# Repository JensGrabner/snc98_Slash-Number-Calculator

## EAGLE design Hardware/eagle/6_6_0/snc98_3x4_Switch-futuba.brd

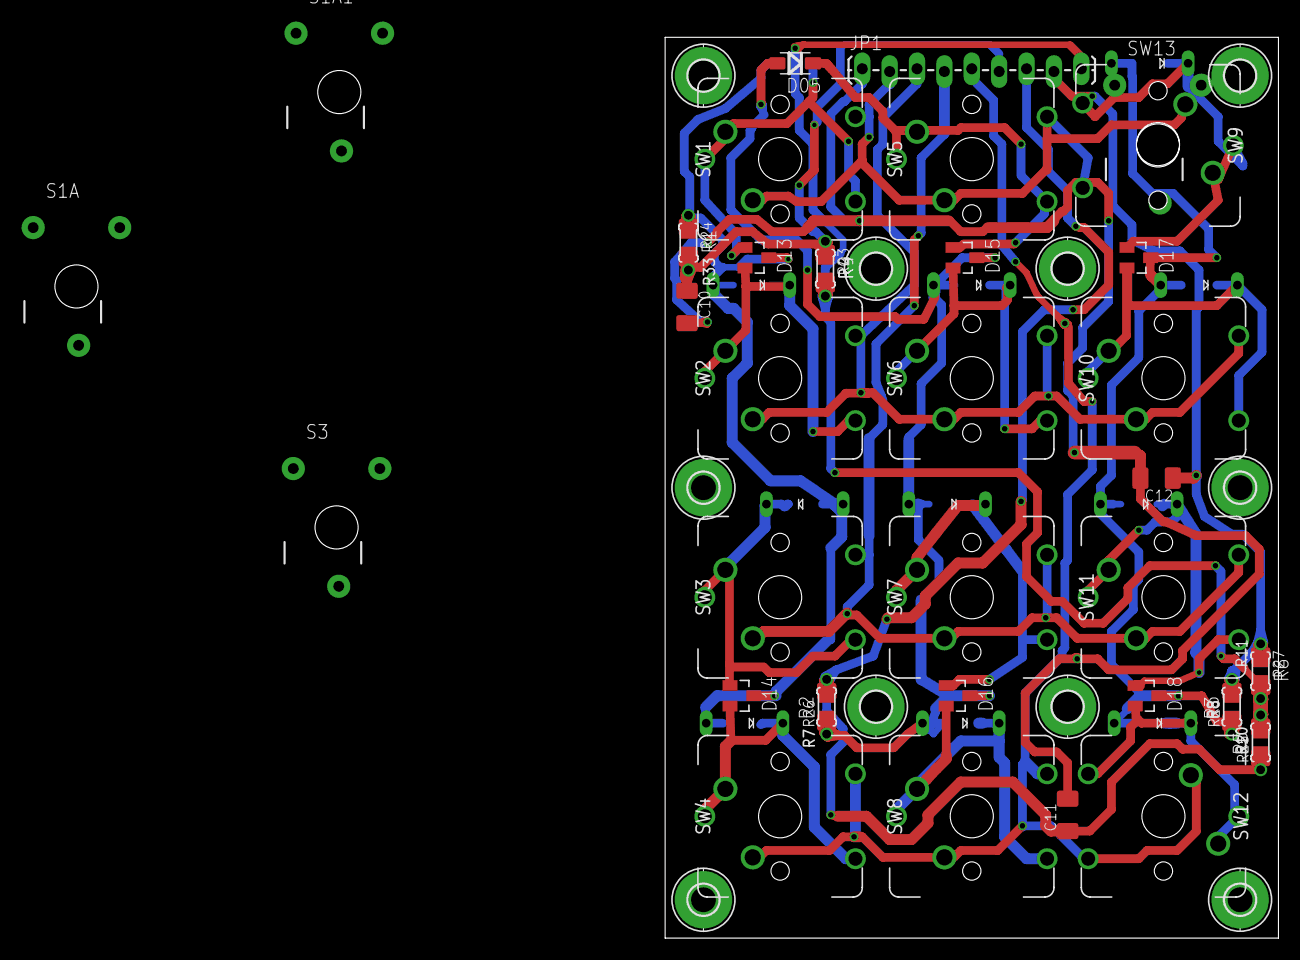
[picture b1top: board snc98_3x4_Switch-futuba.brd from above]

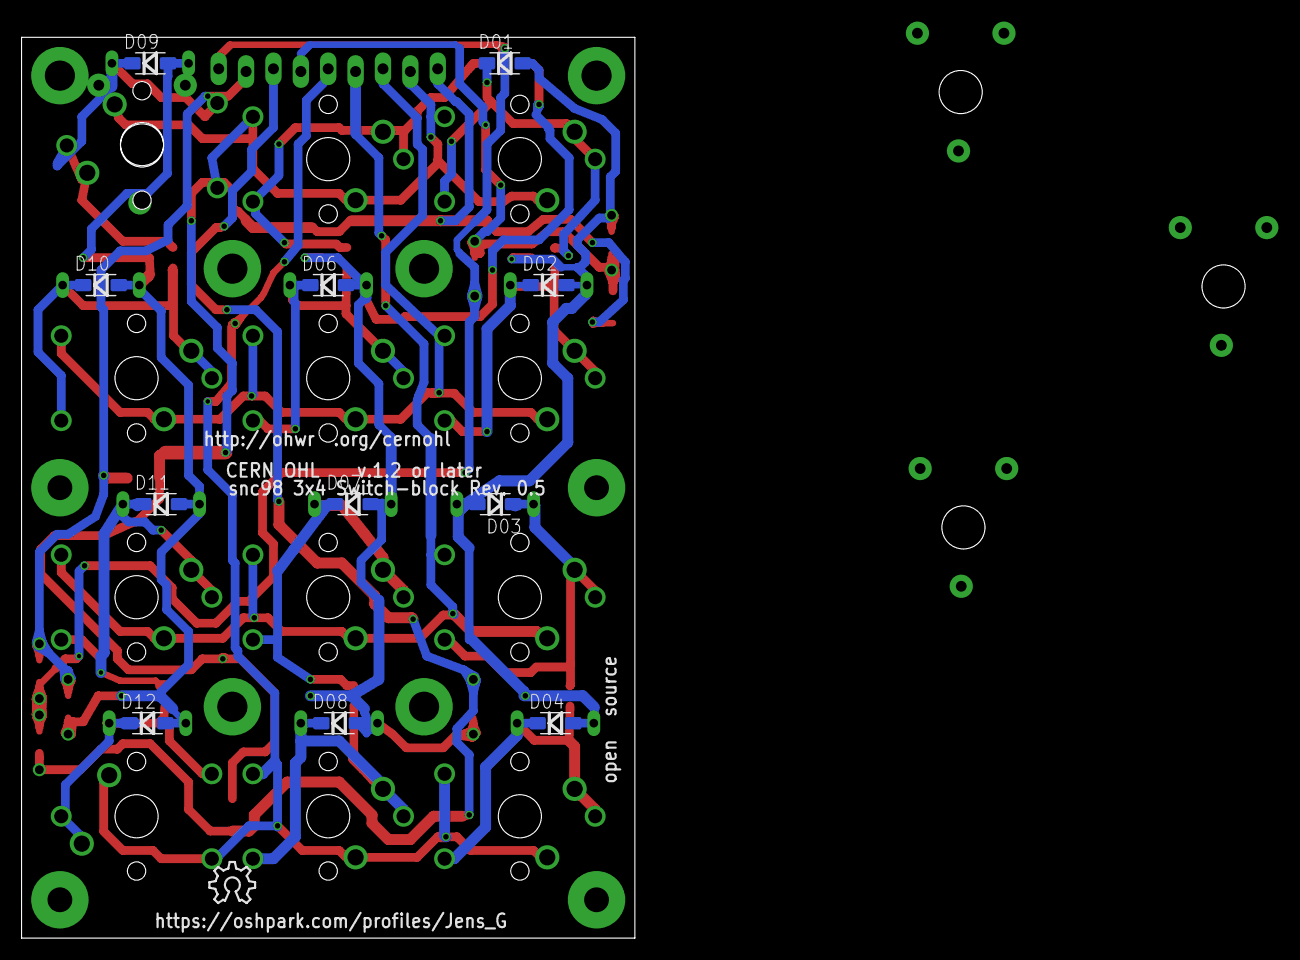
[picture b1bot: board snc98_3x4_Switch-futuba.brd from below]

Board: 2 copper layers, 56.9 x 83.6 mm, 77 parts (12 on the bottom side), 24 nets.

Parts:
C10, C11, C12: 15n; C1206K
D01, D02, D03, D04, D05, D06, D07, D08, D09: SD103AW-DIO; SOD-123F
D10, D11, D12: SD103CW; SOD-123F
D13, D14, D15, D16, D17, D18: BAT54A; SOT23
D19, D20, D21, D22, D23, D24, D25, D26, D27, D28: SD103C; 280MIL-TH
H1, H4, H5, H6, H7, H8: MOUNT-PAD-ROUND2.8; 2,8-PAD
H2, H3, H9, H10: MOUNT-PAD-ROUND2.3; 2,3-PAD
JP1: M09LOCK-LONGPADS; 1X09_LOCK_LONGPADS
LOGO1: OSHW_LOGO_8MILX0150-NT; OSHW_8X150_NOTEXT
R1, R2, R3: 6k8; R1206
R4, R5, R6: 27k; R1206
R7, R8, R33: 6k8; M0805
R9, R10, R11: 27k; M0805
R23, R25, R27: 27k; 0204/5
R24, R26, R28: 6k8; 0204/5
S1A, S1A1, S3: MX1A-XXNN
SW1, SW2, SW3, SW4, SW5, SW6, SW7, SW8, SW9, SW10, SW11, SW12: CHERRY_MX_WITH_FIXING_PINS; MX1A-XXNW
SW13: CHERRY_MX; MX1A-XXNN

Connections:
A1: C10.1, JP1.6, R1.2, R4.1, R9.1, R23.1, R24.2, R33.2
A2: C11.1, JP1.7, R2.2, R5.1, R7.2, R10.1, R25.1, R26.2
A3: C12.1, JP1.8, R3.2, R6.1, R8.2, R11.1, R27.1, R28.2
AREF: JP1.9, R4.2, R5.2, R6.2, R9.2, R10.2, R11.2, R23.2, R25.2, R27.2
A_1: D01.A, D02.A, D03.A, D04.A, D13.3, D14.3, D19.P$1, D20.P$1, D21.P$1, R1.1, R24.1, R33.1
A_2: D05.A, D06.A, D07.A, D08.A, D15.3, D16.3, D22.P$1, D23.P$1, D24.P$1, R2.1, R7.1, R26.1
A_3: D09.A, D10.A, D11.A, D12.A, D17.3, D18.3, D25.P$1, D26.P$1, D27.P$1, D28.P$1, R3.1, R8.1, R28.1
C1: JP1.2, SW1.1, SW1.3, SW5.1, SW5.3, SW9.1, SW9.3
C2: JP1.3, SW2.1, SW2.3, SW6.1, SW6.3, SW10.1, SW10.3
C3: JP1.4, SW3.1, SW3.3, SW7.1, SW7.3, SW11.1, SW11.3
C4: JP1.5, SW4.1, SW4.3, SW8.1, SW8.3, SW12.1, SW12.3
GND: C10.2, C11.2, C12.2, JP1.1
unnamed: D04.C, D14.2, D21.P$2, SW4.2, SW4.4, SW4.5
unnamed: D01.C, D13.1, SW1.2, SW1.4, SW1.5
unnamed: D09.C, D17.1, D25.P$2, SW9.2, SW9.4, SW9.5
unnamed: D10.C, D17.2, D26.P$2, SW10.2, SW10.4, SW10.5
unnamed: D02.C, D13.2, D19.P$2, SW2.2, SW2.4, SW2.5
unnamed: D11.C, D18.1, D27.P$2, SW11.2, SW11.4, SW11.5
unnamed: D12.C, D18.2, D28.P$2, SW12.2, SW12.4, SW12.5
unnamed: D05.C, D15.1, SW5.2, SW5.4, SW5.5
unnamed: D06.C, D15.2, D22.P$2, SW6.2, SW6.4, SW6.5
unnamed: D07.C, D16.1, D23.P$2, SW7.2, SW7.4, SW7.5
unnamed: D08.C, D16.2, D24.P$2, SW8.2, SW8.4, SW8.5
unnamed: D03.C, D14.1, D20.P$2, SW3.2, SW3.4, SW3.5

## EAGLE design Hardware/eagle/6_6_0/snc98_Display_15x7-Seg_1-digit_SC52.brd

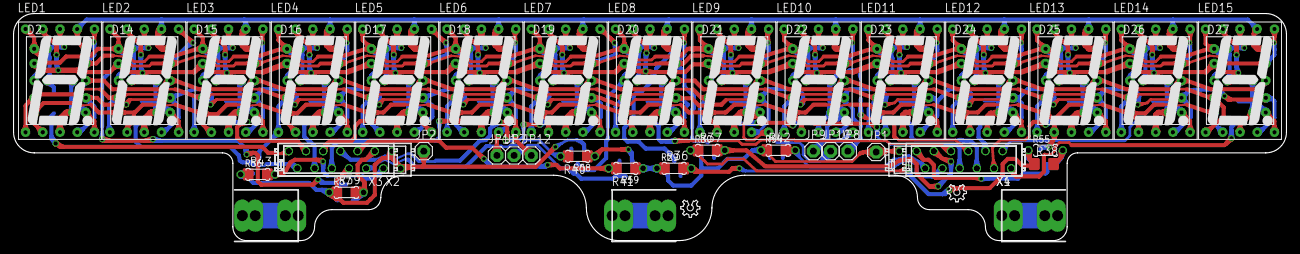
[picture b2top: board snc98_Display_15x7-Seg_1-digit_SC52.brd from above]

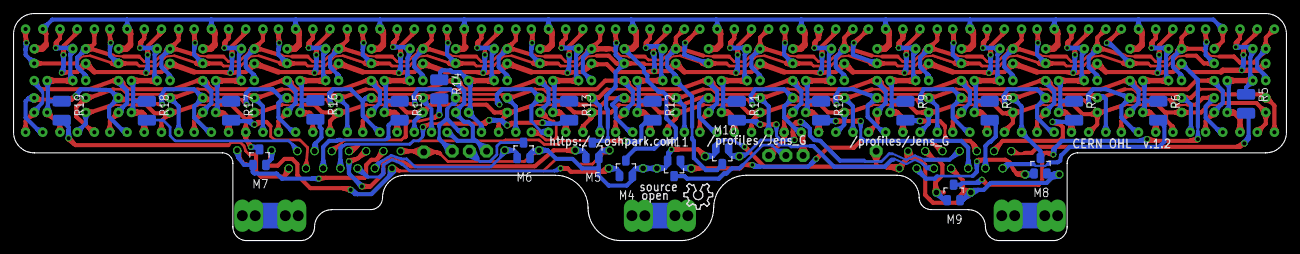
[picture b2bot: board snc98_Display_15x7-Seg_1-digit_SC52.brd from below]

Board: 2 copper layers, 188.0 x 33.5 mm, 87 parts (24 on the bottom side), 52 nets.

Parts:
BH4, BH5: HOLDER_AAA_LEFT1; BATTERY-AAA-LEFT
BH6: HOLDER_AAA_RIGHT; BATTERY-AAA-RIGHT
D2, D14, D15, D16, D17, D18, D19, D20, D21, D22, D23, D24, D25, D26, D27: SC40-11_UNISC40-11_UNI; 10MM_UNI
JP1, JP2, JP7, JP8, JP9, JP10, JP11, JP12: 1X01
LED1, LED2, LED3, LED4, LED5, LED6, LED7, LED8, LED9, LED10, LED11, LED12, LED13, LED14, LED15: 7-SEG_SC52-11; SA52-11
LOGO1: OSHW_LOGO_8MILX0150-NT; OSHW_8X150_NOTEXT
LOGO2, LOGO3: OSHW_LOGO_6MILX0100-NT; OSHW_6X100_NOTEXT
M4, M5, M6, M7, M8, M9, M10, M11: IRLML2244; SOT-23
R5, R6, R7, R8, R9, R10, R11, R12, R13, R14, R15, R16, R17, R18, R19: 22; R1210
R29, R30, R54, R55, R56, R57, R58, R59: 3k3; 0204/5
R36, R37, R38, R39, R40, R41, R42, R43: 3k3; R1206
X1, X3: MICROMATCH-12
X2, X4: MICROMATCH-14

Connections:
CA_LED: JP1.1, JP2.1, M4.2, M5.2, M6.2, M7.2, M8.2, M9.2, M10.2, M11.2, R29.1, R30.1, R36.1, R37.1, R38.1, R39.1, R40.1, R41.1, R42.1, R43.1, R54.1, R55.1, R56.1, R57.1, R58.1, R59.1, X2.8, X2.13, X2.14, X3.8, X4.1, X4.2
D0_A: R5.2, X2.1, X3.1
D1_A: R6.2, X2.2, X3.2
D2_A: R7.2, X2.3, X3.3
D3_A: R8.2, X2.4, X3.4
D4_A: R9.2, X2.5, X3.5
D5_A: R10.2, X2.6, X3.6
D6_A: R11.2, X2.7, X3.7
D7_A: R12.2, X1.5, X4.7
D8_A: R13.2, X1.6, X4.8
D9_A: R14.2, X1.7, X4.9
D10_A: R15.2, X1.8, X4.10
D11_A: R16.2, X1.9, X4.11
D12_A: R17.2, X1.10, X4.12
D13_A: R18.2, X1.11, X4.13
D14_A: R19.2, X1.12, X4.14
DIG_0: D2.11, D2.12, D2.13, D2.14, LED1.3, LED1.8, R5.1
DIG_1: D14.11, D14.12, D14.13, D14.14, LED2.3, LED2.8, R6.1
DIG_2: D15.11, D15.12, D15.13, D15.14, LED3.3, LED3.8, R7.1
DIG_3: D16.11, D16.12, D16.13, D16.14, LED4.3, LED4.8, R8.1
DIG_4: D17.11, D17.12, D17.13, D17.14, LED5.3, LED5.8, R9.1
DIG_5: D18.11, D18.12, D18.13, D18.14, LED6.3, LED6.8, R10.1
DIG_6: D19.11, D19.12, D19.13, D19.14, LED7.3, LED7.8, R11.1
DIG_7: D20.11, D20.12, D20.13, D20.14, LED8.3, LED8.8, R12.1
DIG_8: D21.11, D21.12, D21.13, D21.14, LED9.3, LED9.8, R13.1
DIG_9: D22.11, D22.12, D22.13, D22.14, LED10.3, LED10.8, R14.1
DIG_10: D23.11, D23.12, D23.13, D23.14, LED11.3, LED11.8, R15.1
DIG_11: D24.11, D24.12, D24.13, D24.14, LED12.3, LED12.8, R16.1
DIG_12: D25.11, D25.12, D25.13, D25.14, LED13.3, LED13.8, R17.1
DIG_13: D26.11, D26.12, D26.13, D26.14, LED14.3, LED14.8, R18.1
DIG_14: D27.11, D27.12, D27.13, D27.14, LED15.3, LED15.8, R19.1
IO-A: M4.1, R29.2, R36.2, X1.4, X4.6
IO-B: M5.1, R30.2, R37.2, X1.3, X4.5
IO-C: M6.1, R42.2, R54.2, X1.2, X4.4
IO-D: M7.1, R38.2, R55.2, X1.1, X4.3
IO-DP: M11.1, R41.2, R59.2, X2.9, X3.9
IO-E: M8.1, R43.2, R56.2, X2.12, X3.12
IO-F: M9.1, R39.2, R57.2, X2.11, X3.11
IO-G: M10.1, R40.2, R58.2, X2.10, X3.10
NC1: BH4.P1, BH4.P2, BH4.P3, BH4.P4
NC2: BH5.P1, BH5.P2, BH5.P3, BH5.P4
NC3: BH6.M1, BH6.M2, BH6.M3, BH6.M4
SEG_A: D2.10, D14.10, D15.10, D16.10, D17.10, D18.10, D19.10, D20.10, D21.10, D22.10, D23.10, D24.10, D25.10, D26.10, D27.10, LED1.7, LED2.7, LED3.7, LED4.7, LED5.7, LED6.7, LED7.7, LED8.7, LED9.7, LED10.7, LED11.7, LED12.7, LED13.7, LED14.7, LED15.7, M4.3
SEG_B: D2.9, D14.9, D15.9, D16.9, D17.9, D18.9, D19.9, D20.9, D21.9, D22.9, D23.9, D24.9, D25.9, D26.9, D27.9, LED1.6, LED2.6, LED3.6, LED4.6, LED5.6, LED6.6, LED7.6, LED8.6, LED9.6, LED10.6, LED11.6, LED12.6, LED13.6, LED14.6, LED15.6, M5.3
SEG_C: D2.7, D14.7, D15.7, D16.7, D17.7, D18.7, D19.7, D20.7, D21.7, D22.7, D23.7, D24.7, D25.7, D26.7, D27.7, JP8.1, JP11.1, LED1.4, LED2.4, LED3.4, LED4.4, LED5.4, LED6.4, LED7.4, LED8.4, LED9.4, LED10.4, LED11.4, LED12.4, LED13.4, LED14.4, LED15.4
SEG_C_SOURCE: JP10.1, M6.3
SEG_D: D2.5, D14.5, D15.5, D16.5, D17.5, D18.5, D19.5, D20.5, D21.5, D22.5, D23.5, D24.5, D25.5, D26.5, D27.5, LED1.2, LED2.2, LED3.2, LED4.2, LED5.2, LED6.2, LED7.2, LED8.2, LED9.2, LED10.2, LED11.2, LED12.2, LED13.2, LED14.2, LED15.2, M7.3
SEG_DP: D2.6, D2.8, D14.6, D14.8, D15.6, D15.8, D16.6, D16.8, D17.6, D17.8, D18.6, D18.8, D19.6, D19.8, D20.6, D20.8, D21.6, D21.8, D22.6, D22.8, D23.6, D23.8, D24.6, D24.8, D25.6, D25.8, D26.6, D26.8, D27.6, D27.8, JP9.1, JP12.1, LED1.5, LED2.5, LED3.5, LED4.5, LED5.5, LED6.5, LED7.5, LED8.5, LED9.5, LED10.5, LED11.5, LED12.5, LED13.5, LED14.5, LED15.5
SEG_DP_SOURCE: JP7.1, M11.3
SEG_E: D2.4, D14.4, D15.4, D16.4, D17.4, D18.4, D19.4, D20.4, D21.4, D22.4, D23.4, D24.4, D25.4, D26.4, D27.4, LED1.1, LED2.1, LED3.1, LED4.1, LED5.1, LED6.1, LED7.1, LED8.1, LED9.1, LED10.1, LED11.1, LED12.1, LED13.1, LED14.1, LED15.1, M8.3
SEG_F: D2.2, D14.2, D15.2, D16.2, D17.2, D18.2, D19.2, D20.2, D21.2, D22.2, D23.2, D24.2, D25.2, D26.2, D27.2, LED1.9, LED2.9, LED3.9, LED4.9, LED5.9, LED6.9, LED7.9, LED8.9, LED9.9, LED10.9, LED11.9, LED12.9, LED13.9, LED14.9, LED15.9, M9.3
SEG_G: D2.1, D2.3, D14.1, D14.3, D15.1, D15.3, D16.1, D16.3, D17.1, D17.3, D18.1, D18.3, D19.1, D19.3, D20.1, D20.3, D21.1, D21.3, D22.1, D22.3, D23.1, D23.3, D24.1, D24.3, D25.1, D25.3, D26.1, D26.3, D27.1, D27.3, LED1.10, LED2.10, LED3.10, LED4.10, LED5.10, LED6.10, LED7.10, LED8.10, LED9.10, LED10.10, LED11.10, LED12.10, LED13.10, LED14.10, LED15.10, M10.3

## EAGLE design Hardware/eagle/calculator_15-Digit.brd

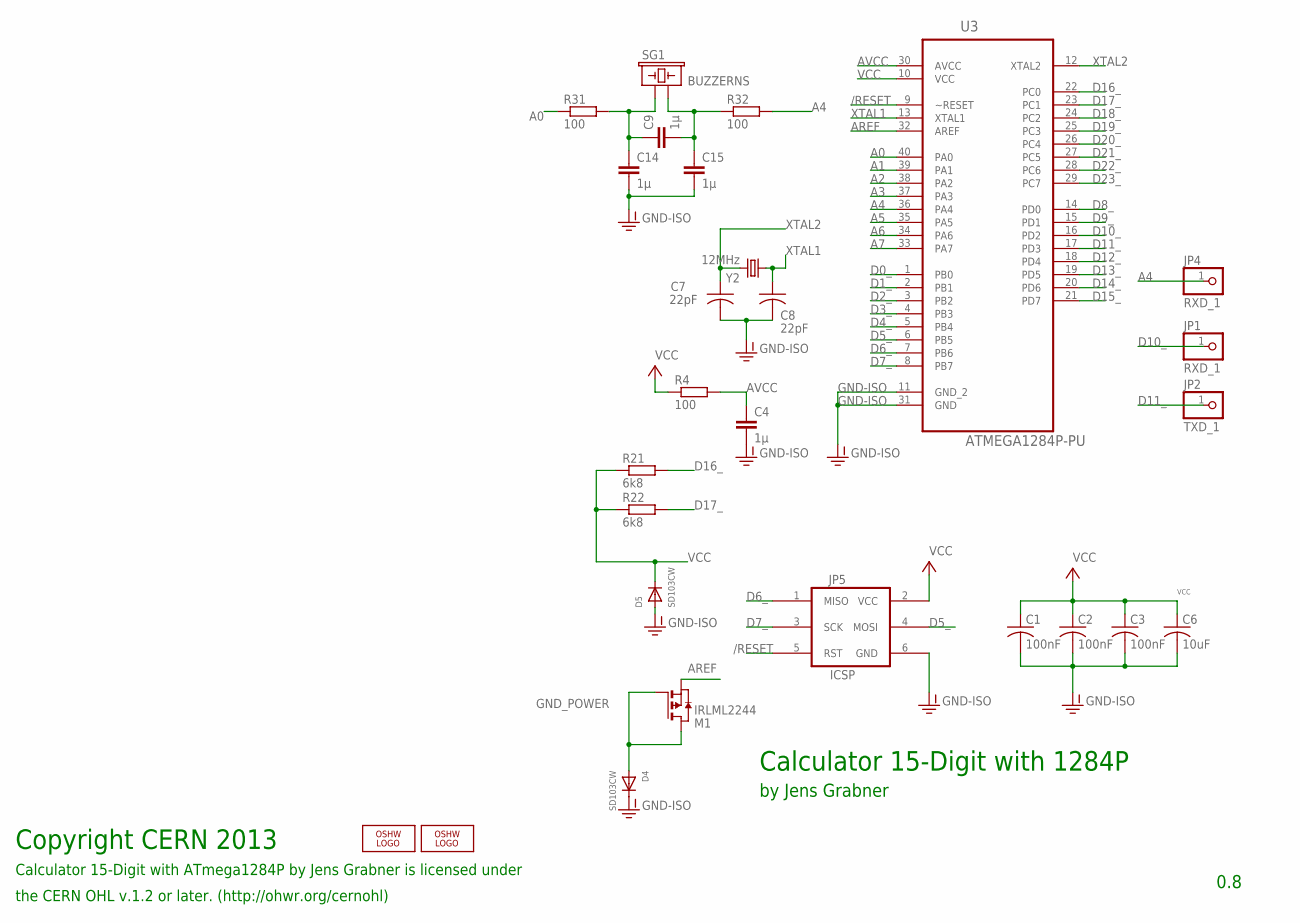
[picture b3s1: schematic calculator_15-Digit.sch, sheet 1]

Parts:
C1, C2, C3: 100nF; C025_050-025X075
C4, C9, C14, C15: 1µ; C025_050-025X075
C6: 10uF; C025_050-025X075
C7, C8: 22pF; C025-024X044
D4, D5: SD103CW; SMADIODE
JP1, JP4: RXD_1; 1X01-CLEANBIG
JP2: TXD_1; 1X01-CLEANBIG
JP5: ICSP; 2X3_LOCK
LOGO1: OSHW_LOGO_8MILX0150-NT; OSHW_8X150_NOTEXT
LOGO2: OSHW_LOGO_6MILX0100-NT; OSHW_6X100_NOTEXT
M1: IRLML2244; SOT-23
R4, R31, R32: 100; 0204/7
R21, R22: 6k8; 0204/7
SG1: BUZZERNS; BUZZER-12MM-NS
U3: ATMEGA1284P-PU; DIP254P1524X483-40
Y2: 12MHz; HC49U-V

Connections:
/RESET: JP5.5 (RST), U3.9 (~RESET); also elsewhere on the board
A0: R31.1, U3.40 (PA0)
A1: U3.39 (PA1); also elsewhere on the board
A2: U3.38 (PA2); also elsewhere on the board
A3: U3.37 (PA3); also elsewhere on the board
A4: JP4.1, R32.2, U3.36 (PA4)
A5: U3.35 (PA5); also elsewhere on the board
A6: U3.34 (PA6); also elsewhere on the board
A7: U3.33 (PA7); also elsewhere on the board
AREF: M1.2 (S), U3.32 (AREF); also elsewhere on the board
AVCC: C4.1, R4.2, U3.30 (AVCC)
D0_: U3.1 (PB0); also elsewhere on the board
D1_: U3.2 (PB1); also elsewhere on the board
D2_: U3.3 (PB2)
D3_: U3.4 (PB3); also elsewhere on the board
D4_: U3.5 (PB4)
D5_: JP5.4 (MOSI), U3.6 (PB5)
D6_: JP5.1 (MISO), U3.7 (PB6); also elsewhere on the board
D7_: JP5.3 (SCK), U3.8 (PB7); also elsewhere on the board
D8_: U3.14 (PD0); also elsewhere on the board
D9_: U3.15 (PD1); also elsewhere on the board
D10_: JP1.1, U3.16 (PD2); also elsewhere on the board
D11_: JP2.1, U3.17 (PD3); also elsewhere on the board
D12_: U3.18 (PD4); also elsewhere on the board
D13_: U3.19 (PD5); also elsewhere on the board
D14_: U3.20 (PD6); also elsewhere on the board
D15_: U3.21 (PD7); also elsewhere on the board
D16_: R21.2, U3.22 (PC0)
D17_: R22.2, U3.23 (PC1)
D18_: U3.24 (PC2); also elsewhere on the board
D19_: U3.25 (PC3); also elsewhere on the board
D20_: U3.26 (PC4); also elsewhere on the board
D21_: U3.27 (PC5); also elsewhere on the board
D22_: U3.28 (PC6); also elsewhere on the board
D23_: U3.29 (PC7); also elsewhere on the board
GND-ISO: C1.2, C2.2, C3.2, C4.2, C6.2, C7.2, C8.2, C14.2, C15.2, D4.C, D5.A, JP5.6 (GND), U3.11 (GND_2), U3.31 (GND); also elsewhere on the board
GND_POWER: D4.A, M1.1 (G), M1.3 (D)
unnamed: C9.2, C15.1, R32.1, SG1.- (2)
unnamed: C9.1, C14.1, R31.2, SG1.+ (1)
VCC: C1.1, C2.1, C3.1, C6.1, D5.C, JP5.2 (VCC), R4.1, R21.1, R22.1, U3.10 (VCC); also elsewhere on the board
XTAL1: C8.1, U3.13 (XTAL1), Y2.1
XTAL2: C7.1, U3.12 (XTAL2), Y2.2

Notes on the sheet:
Calculator 15-Digit with 1284P
by Jens Grabner
0.8
Calculator 15-Digit with ATmega1284P by Jens Grabner is licensed under
Copyright CERN 2013
the CERN OHL v.1.2 or later. (http://ohwr.org/cernohl)

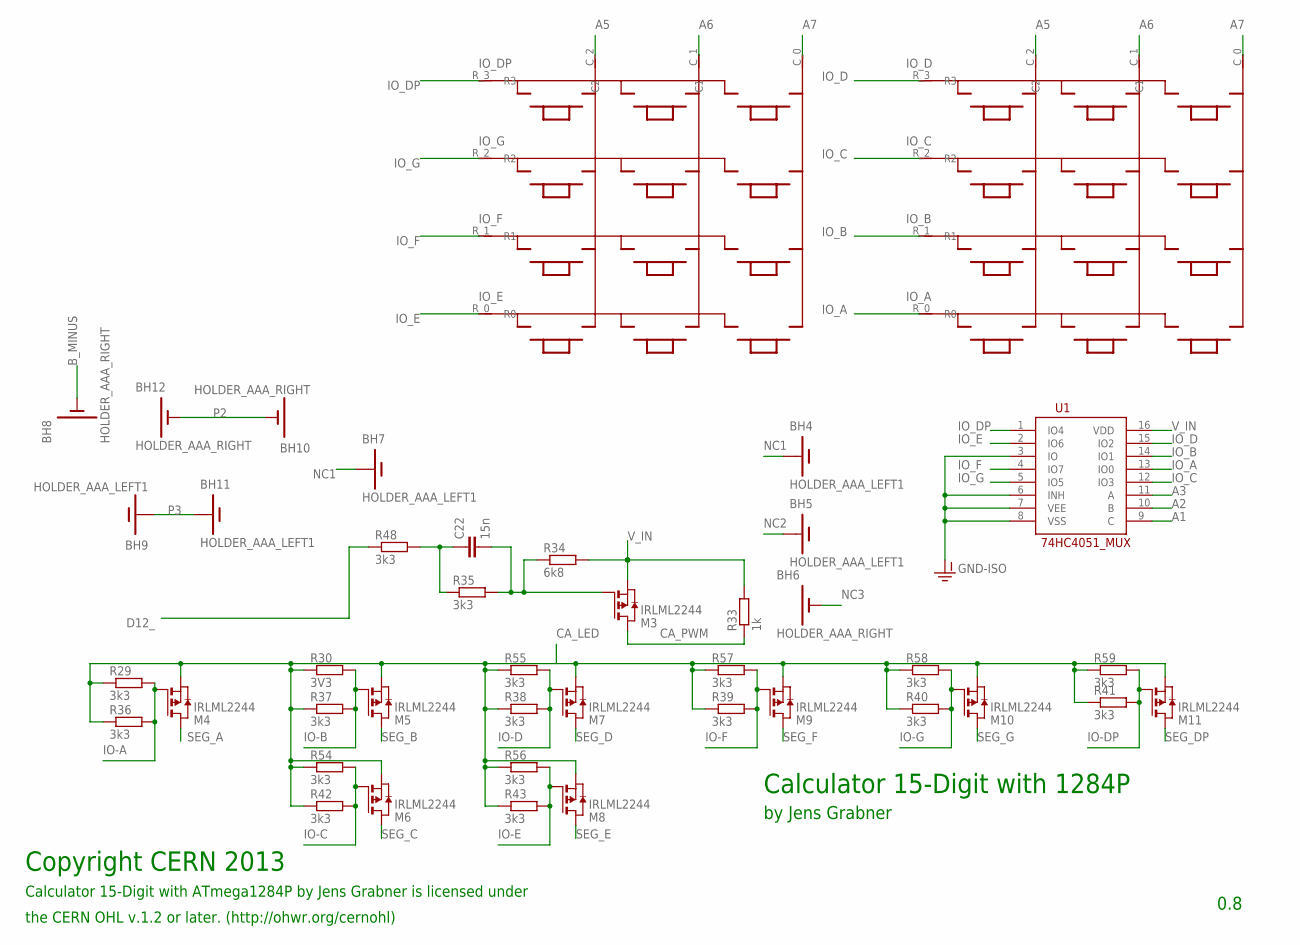
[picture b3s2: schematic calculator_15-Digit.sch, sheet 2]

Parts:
BH4, BH5, BH7, BH9, BH11: HOLDER_AAA_LEFT1; BATTERY-AAA-LEFT
BH6, BH8, BH10, BH12: HOLDER_AAA_RIGHT; BATTERY-AAA-RIGHT
C22: 15n; C1206K
KP1, KP2: KEYPAD
M3, M4, M5, M6, M7, M8, M9, M10, M11: IRLML2244; SOT-23
R29, R54, R55, R56, R57, R58, R59: 3k3; 0204/5
R30: 3V3; 0204/5
R33: 1k; 0204/7
R34: 6k8; 0204/7
R35, R48: 3k3; 0204/7
R36, R37, R38, R39, R40, R41, R42, R43: 3k3; R1206
U1: 74HC4051_MUX; SO16

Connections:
A1: U1.9 (C); also elsewhere on the board
A2: U1.10 (B); also elsewhere on the board
A3: U1.11 (A); also elsewhere on the board
A5: KP1.C_2 (C2), KP2.C_2 (C2); also elsewhere on the board
A6: KP1.C_1 (C1), KP2.C_1 (C1); also elsewhere on the board
A7: KP1.C_0 (C0), KP2.C_0 (C0); also elsewhere on the board
A8: C22.1, R35.1, R48.2
B_MINUS: BH8.M1, BH8.M2, BH8.M3, BH8.M4; also elsewhere on the board
CA_LED: M4.2 (S), M5.2 (S), M6.2 (S), M7.2 (S), M8.2 (S), M9.2 (S), M10.2 (S), M11.2 (S), R29.1, R30.1, R36.1, R37.1, R38.1, R39.1, R40.1, R41.1, R42.1, R43.1, R54.1, R55.1, R56.1, R57.1, R58.1, R59.1; also elsewhere on the board
CA_PWM: M3.3 (D), R33.1; also elsewhere on the board
D12_: R48.1; also elsewhere on the board
GND1: C22.2
GND-ISO: U1.3 (IO), U1.6 (INH), U1.7 (VEE), U1.8 (VSS); also elsewhere on the board
IO-A: M4.1 (G), R29.2, R36.2; also elsewhere on the board
IO-B: M5.1 (G), R30.2, R37.2; also elsewhere on the board
IO-C: M6.1 (G), R42.2, R54.2; also elsewhere on the board
IO-D: M7.1 (G), R38.2, R55.2; also elsewhere on the board
IO-DP: M11.1 (G), R41.2, R59.2; also elsewhere on the board
IO-E: M8.1 (G), R43.2, R56.2; also elsewhere on the board
IO-F: M9.1 (G), R39.2, R57.2; also elsewhere on the board
IO-G: M10.1 (G), R40.2, R58.2; also elsewhere on the board
IO_A: KP2.R_0 (R0), U1.13 (IO0); also elsewhere on the board
IO_B: KP2.R_1 (R1), U1.14 (IO1); also elsewhere on the board
IO_C: KP2.R_2 (R2), U1.12 (IO3); also elsewhere on the board
IO_D: KP2.R_3 (R3), U1.15 (IO2); also elsewhere on the board
IO_DP: KP1.R_3 (R3), U1.1 (IO4); also elsewhere on the board
IO_E: KP1.R_0 (R0), U1.2 (IO6); also elsewhere on the board
IO_F: KP1.R_1 (R1), U1.4 (IO7); also elsewhere on the board
IO_G: KP1.R_2 (R2), U1.5 (IO5); also elsewhere on the board
unnamed: M3.1 (G), R34.1, R35.2
NC1: BH4.P1, BH4.P2, BH4.P3, BH4.P4, BH7.P1, BH7.P2, BH7.P3, BH7.P4
NC2: BH5.P1, BH5.P2, BH5.P3, BH5.P4
NC3: BH6.M1, BH6.M2, BH6.M3, BH6.M4
P2: BH10.M1, BH10.M2, BH10.M3, BH10.M4, BH12.M1, BH12.M2, BH12.M3, BH12.M4
P3: BH9.P1, BH9.P2, BH9.P3, BH9.P4, BH11.P1, BH11.P2, BH11.P3, BH11.P4
SEG_A: M4.3 (D); also elsewhere on the board
SEG_B: M5.3 (D); also elsewhere on the board
SEG_C: M6.3 (D); also elsewhere on the board
SEG_D: M7.3 (D); also elsewhere on the board
SEG_DP: M11.3 (D); also elsewhere on the board
SEG_E: M8.3 (D); also elsewhere on the board
SEG_F: M9.3 (D); also elsewhere on the board
SEG_G: M10.3 (D); also elsewhere on the board
V_IN: M3.2 (S), R33.2, R34.2, U1.16 (VDD); also elsewhere on the board

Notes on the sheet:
Calculator 15-Digit with 1284P
by Jens Grabner
0.8
Calculator 15-Digit with ATmega1284P by Jens Grabner is licensed under
Copyright CERN 2013
the CERN OHL v.1.2 or later. (http://ohwr.org/cernohl)

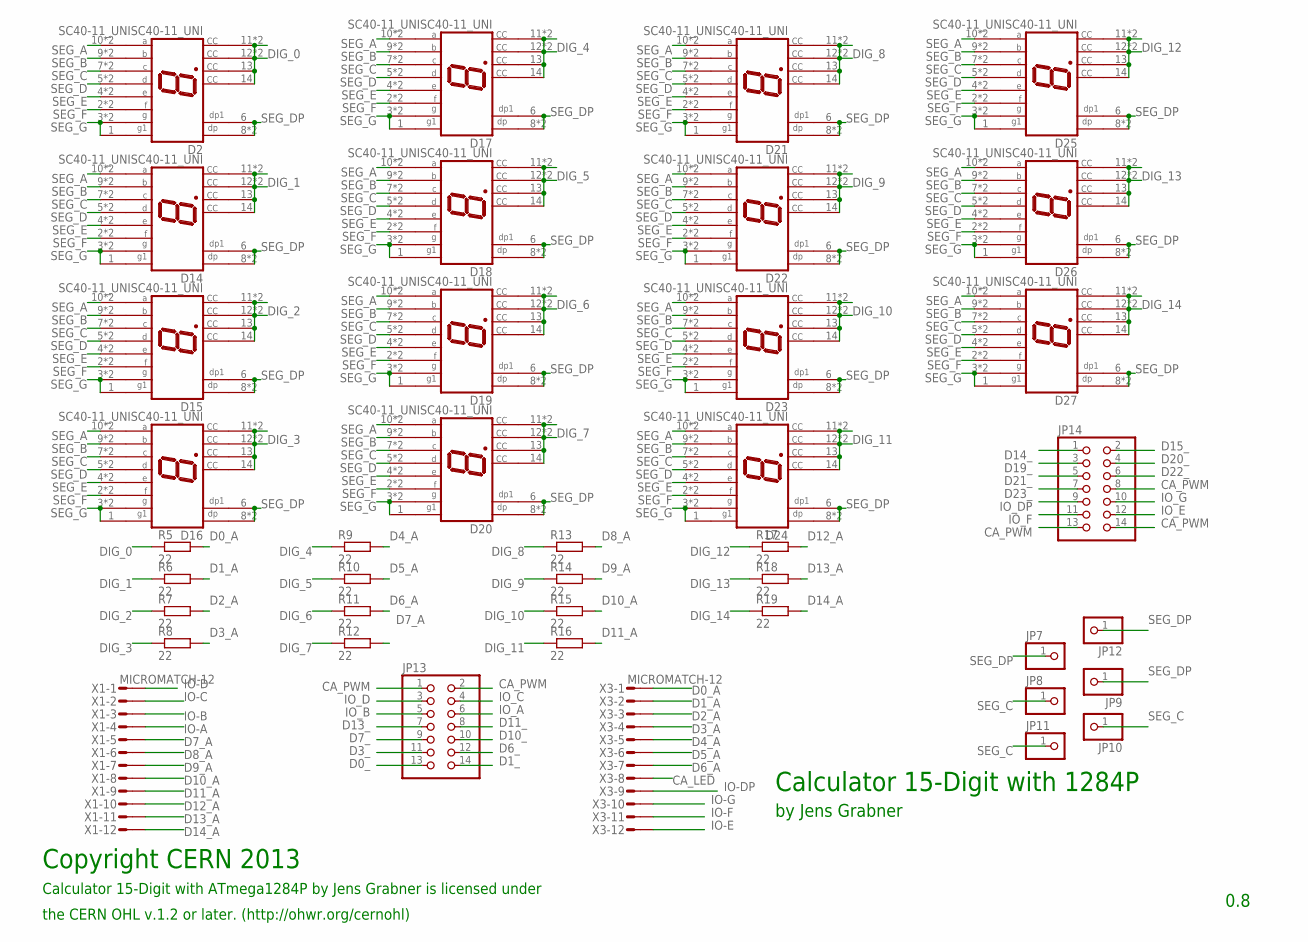
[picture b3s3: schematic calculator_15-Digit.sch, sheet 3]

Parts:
D2, D14, D15, D16, D17, D18, D19, D20, D21, D22, D23, D24, D25, D26, D27: SC40-11_UNISC40-11_UNI; 10MM_UNI
JP7, JP8, JP9, JP10, JP11, JP12: PINHD-1X1; 1X01
JP13, JP14: PINHD-2X7; 2X07
R5, R6, R7, R8, R9, R10, R11, R12, R13, R14, R15, R16, R17, R18, R19: 22; R1210
X1, X3: MICROMATCH-12

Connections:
CA_LED: X3.8; also elsewhere on the board
CA_PWM: JP13.1, JP13.2, JP14.8, JP14.13, JP14.14; also elsewhere on the board
D0_: JP13.13; also elsewhere on the board
D0_A: R5.2, X3.1
D1_: JP13.14; also elsewhere on the board
D1_A: R6.2, X3.2
D2_A: R7.2, X3.3
D3_: JP13.11; also elsewhere on the board
D3_A: R8.2, X3.4
D4_A: R9.2, X3.5
D5_A: R10.2, X3.6
D6_: JP13.12; also elsewhere on the board
D6_A: R11.2, X3.7
D7_: JP13.9; also elsewhere on the board
D7_A: R12.2, X1.5
D8_A: R13.2, X1.6
D9_A: R14.2, X1.7
D10_: JP13.10; also elsewhere on the board
D10_A: R15.2, X1.8
D11_: JP13.8; also elsewhere on the board
D11_A: R16.2, X1.9
D12_A: R17.2, X1.10
D13_: JP13.7; also elsewhere on the board
D13_A: R18.2, X1.11
D14_: JP14.1; also elsewhere on the board
D14_A: R19.2, X1.12
D15_: JP14.2; also elsewhere on the board
D19_: JP14.3; also elsewhere on the board
D20_: JP14.4; also elsewhere on the board
D21_: JP14.5; also elsewhere on the board
D22_: JP14.6; also elsewhere on the board
D23_: JP14.7; also elsewhere on the board
DIG_0: D2.11 (CC1), D2.12 (CC2), D2.13 (CC3), D2.14 (CC4), D2.23 (CC1), D2.28 (CC2), R5.1
DIG_1: D14.11 (CC1), D14.12 (CC2), D14.13 (CC3), D14.14 (CC4), D14.23 (CC1), D14.28 (CC2), R6.1
DIG_2: D15.11 (CC1), D15.12 (CC2), D15.13 (CC3), D15.14 (CC4), D15.23 (CC1), D15.28 (CC2), R7.1
DIG_3: D16.11 (CC1), D16.12 (CC2), D16.13 (CC3), D16.14 (CC4), D16.23 (CC1), D16.28 (CC2), R8.1
DIG_4: D17.11 (CC1), D17.12 (CC2), D17.13 (CC3), D17.14 (CC4), D17.23 (CC1), D17.28 (CC2), R9.1
DIG_5: D18.11 (CC1), D18.12 (CC2), D18.13 (CC3), D18.14 (CC4), D18.23 (CC1), D18.28 (CC2), R10.1
DIG_6: D19.11 (CC1), D19.12 (CC2), D19.13 (CC3), D19.14 (CC4), D19.23 (CC1), D19.28 (CC2), R11.1
DIG_7: D20.11 (CC1), D20.12 (CC2), D20.13 (CC3), D20.14 (CC4), D20.23 (CC1), D20.28 (CC2), R12.1
DIG_8: D21.11 (CC1), D21.12 (CC2), D21.13 (CC3), D21.14 (CC4), D21.23 (CC1), D21.28 (CC2), R13.1
DIG_9: D22.11 (CC1), D22.12 (CC2), D22.13 (CC3), D22.14 (CC4), D22.23 (CC1), D22.28 (CC2), R14.1
DIG_10: D23.11 (CC1), D23.12 (CC2), D23.13 (CC3), D23.14 (CC4), D23.23 (CC1), D23.28 (CC2), R15.1
DIG_11: D24.11 (CC1), D24.12 (CC2), D24.13 (CC3), D24.14 (CC4), D24.23 (CC1), D24.28 (CC2), R16.1
DIG_12: D25.11 (CC1), D25.12 (CC2), D25.13 (CC3), D25.14 (CC4), D25.23 (CC1), D25.28 (CC2), R17.1
DIG_13: D26.11 (CC1), D26.12 (CC2), D26.13 (CC3), D26.14 (CC4), D26.23 (CC1), D26.28 (CC2), R18.1
DIG_14: D27.11 (CC1), D27.12 (CC2), D27.13 (CC3), D27.14 (CC4), D27.23 (CC1), D27.28 (CC2), R19.1
IO-A: X1.4; also elsewhere on the board
IO-B: X1.3; also elsewhere on the board
IO-C: X1.2; also elsewhere on the board
IO-D: X1.1; also elsewhere on the board
IO-DP: X3.9; also elsewhere on the board
IO-E: X3.12; also elsewhere on the board
IO-F: X3.11; also elsewhere on the board
IO-G: X3.10; also elsewhere on the board
IO_A: JP13.6; also elsewhere on the board
IO_B: JP13.5; also elsewhere on the board
IO_C: JP13.4; also elsewhere on the board
IO_D: JP13.3; also elsewhere on the board
IO_DP: JP14.9; also elsewhere on the board
IO_E: JP14.12; also elsewhere on the board
IO_F: JP14.11; also elsewhere on the board
IO_G: JP14.10; also elsewhere on the board
SEG_A: D2.10 (A), D2.27 (A), D14.10 (A), D14.27 (A), D15.10 (A), D15.27 (A), D16.10 (A), D16.27 (A), D17.10 (A), D17.27 (A), D18.10 (A), D18.27 (A), D19.10 (A), D19.27 (A), D20.10 (A), D20.27 (A), D21.10 (A), D21.27 (A), D22.10 (A), D22.27 (A), D23.10 (A), D23.27 (A), D24.10 (A), D24.27 (A), D25.10 (A), D25.27 (A), D26.10 (A), D26.27 (A), D27.10 (A), D27.27 (A); also elsewhere on the board
SEG_B: D2.9 (B), D2.26 (B), D14.9 (B), D14.26 (B), D15.9 (B), D15.26 (B), D16.9 (B), D16.26 (B), D17.9 (B), D17.26 (B), D18.9 (B), D18.26 (B), D19.9 (B), D19.26 (B), D20.9 (B), D20.26 (B), D21.9 (B), D21.26 (B), D22.9 (B), D22.26 (B), D23.9 (B), D23.26 (B), D24.9 (B), D24.26 (B), D25.9 (B), D25.26 (B), D26.9 (B), D26.26 (B), D27.9 (B), D27.26 (B); also elsewhere on the board
SEG_C: D2.7 (C), D2.24 (C), D14.7 (C), D14.24 (C), D15.7 (C), D15.24 (C), D16.7 (C), D16.24 (C), D17.7 (C), D17.24 (C), D18.7 (C), D18.24 (C), D19.7 (C), D19.24 (C), D20.7 (C), D20.24 (C), D21.7 (C), D21.24 (C), D22.7 (C), D22.24 (C), D23.7 (C), D23.24 (C), D24.7 (C), D24.24 (C), D25.7 (C), D25.24 (C), D26.7 (C), D26.24 (C), D27.7 (C), D27.24 (C), JP8.1, JP10.1, JP11.1; also elsewhere on the board
SEG_D: D2.5 (D), D2.22 (D), D14.5 (D), D14.22 (D), D15.5 (D), D15.22 (D), D16.5 (D), D16.22 (D), D17.5 (D), D17.22 (D), D18.5 (D), D18.22 (D), D19.5 (D), D19.22 (D), D20.5 (D), D20.22 (D), D21.5 (D), D21.22 (D), D22.5 (D), D22.22 (D), D23.5 (D), D23.22 (D), D24.5 (D), D24.22 (D), D25.5 (D), D25.22 (D), D26.5 (D), D26.22 (D), D27.5 (D), D27.22 (D); also elsewhere on the board
SEG_DP: D2.6 (DP1), D2.8 (DP), D2.25 (DP), D14.6 (DP1), D14.8 (DP), D14.25 (DP), D15.6 (DP1), D15.8 (DP), D15.25 (DP), D16.6 (DP1), D16.8 (DP), D16.25 (DP), D17.6 (DP1), D17.8 (DP), D17.25 (DP), D18.6 (DP1), D18.8 (DP), D18.25 (DP), D19.6 (DP1), D19.8 (DP), D19.25 (DP), D20.6 (DP1), D20.8 (DP), D20.25 (DP), D21.6 (DP1), D21.8 (DP), D21.25 (DP), D22.6 (DP1), D22.8 (DP), D22.25 (DP), D23.6 (DP1), D23.8 (DP), D23.25 (DP), D24.6 (DP1), D24.8 (DP), D24.25 (DP), D25.6 (DP1), D25.8 (DP), D25.25 (DP), D26.6 (DP1), D26.8 (DP), D26.25 (DP), D27.6 (DP1), D27.8 (DP), D27.25 (DP), JP7.1, JP9.1, JP12.1; also elsewhere on the board
SEG_E: D2.4 (E), D2.21 (E), D14.4 (E), D14.21 (E), D15.4 (E), D15.21 (E), D16.4 (E), D16.21 (E), D17.4 (E), D17.21 (E), D18.4 (E), D18.21 (E), D19.4 (E), D19.21 (E), D20.4 (E), D20.21 (E), D21.4 (E), D21.21 (E), D22.4 (E), D22.21 (E), D23.4 (E), D23.21 (E), D24.4 (E), D24.21 (E), D25.4 (E), D25.21 (E), D26.4 (E), D26.21 (E), D27.4 (E), D27.21 (E); also elsewhere on the board
SEG_F: D2.2 (F), D2.29 (F), D14.2 (F), D14.29 (F), D15.2 (F), D15.29 (F), D16.2 (F), D16.29 (F), D17.2 (F), D17.29 (F), D18.2 (F), D18.29 (F), D19.2 (F), D19.29 (F), D20.2 (F), D20.29 (F), D21.2 (F), D21.29 (F), D22.2 (F), D22.29 (F), D23.2 (F), D23.29 (F), D24.2 (F), D24.29 (F), D25.2 (F), D25.29 (F), D26.2 (F), D26.29 (F), D27.2 (F), D27.29 (F); also elsewhere on the board
SEG_G: D2.1 (G1), D2.3 (G), D2.30 (G), D14.1 (G1), D14.3 (G), D14.30 (G), D15.1 (G1), D15.3 (G), D15.30 (G), D16.1 (G1), D16.3 (G), D16.30 (G), D17.1 (G1), D17.3 (G), D17.30 (G), D18.1 (G1), D18.3 (G), D18.30 (G), D19.1 (G1), D19.3 (G), D19.30 (G), D20.1 (G1), D20.3 (G), D20.30 (G), D21.1 (G1), D21.3 (G), D21.30 (G), D22.1 (G1), D22.3 (G), D22.30 (G), D23.1 (G1), D23.3 (G), D23.30 (G), D24.1 (G1), D24.3 (G), D24.30 (G), D25.1 (G1), D25.3 (G), D25.30 (G), D26.1 (G1), D26.3 (G), D26.30 (G), D27.1 (G1), D27.3 (G), D27.30 (G); also elsewhere on the board

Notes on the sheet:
Calculator 15-Digit with 1284P
by Jens Grabner
0.8
Calculator 15-Digit with ATmega1284P by Jens Grabner is licensed under
Copyright CERN 2013
the CERN OHL v.1.2 or later. (http://ohwr.org/cernohl)

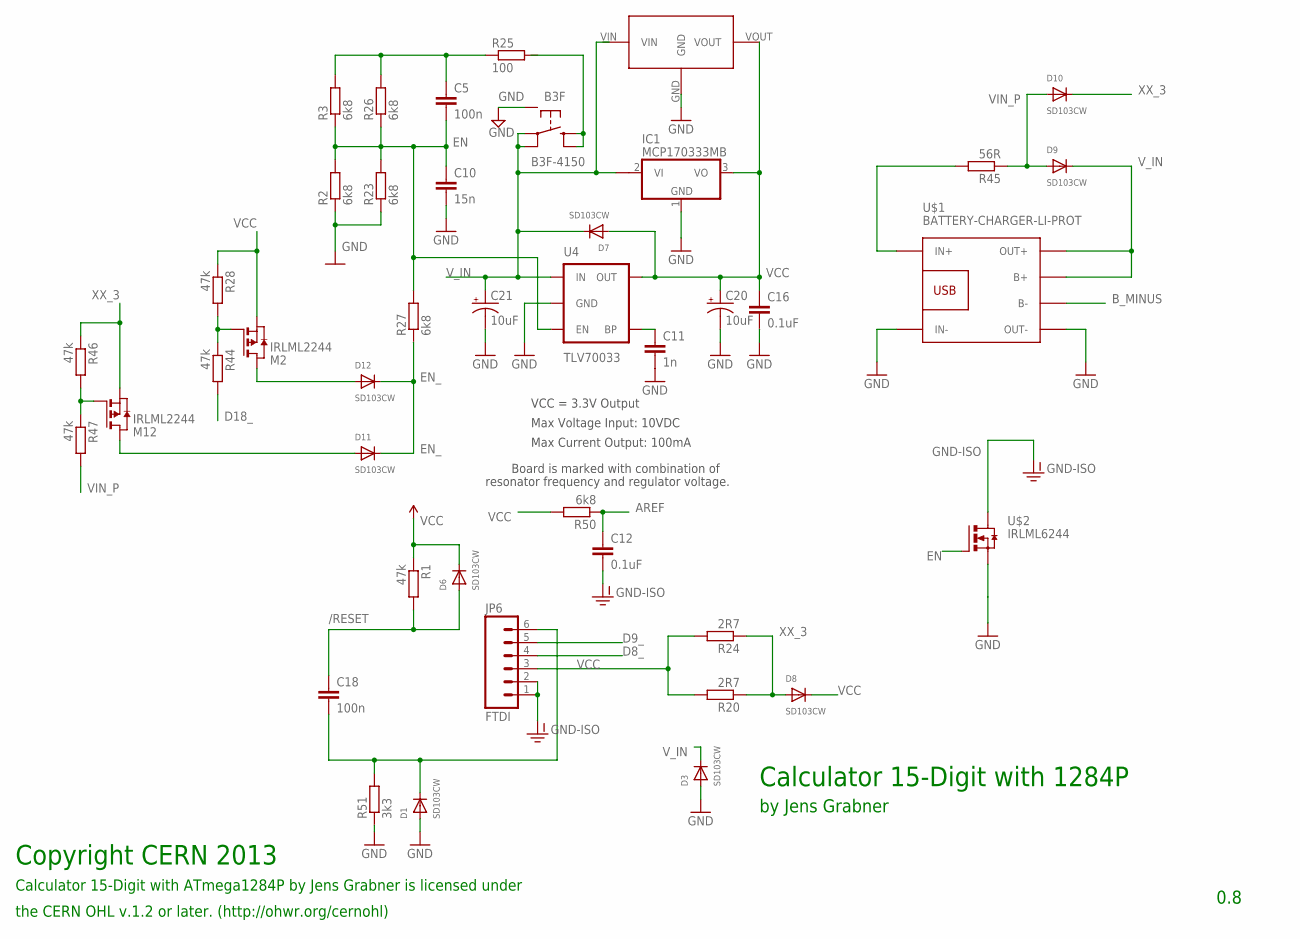
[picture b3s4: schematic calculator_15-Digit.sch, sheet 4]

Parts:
C5: 100n; C1206K
C10: 15n; C1206K
C11: 1n; 0805
C12, C16: 0.1uF; 0805
C18: 100n; C025_050-025X075
C20, C21: 10uF; EIA3216
D1, D3, D6, D7, D8, D9, D10, D11, D12: SD103CW; SMADIODE
IC1: MCP170333MB; SOT89
JP6: FTDI; 1X06_LOCK
M2, M12: IRLML2244; SOT-23
R1, R28, R44, R46, R47: 47k; 0204/7
R2, R26: 6k8; 0204/5
R3, R23, R27: 6k8; R1206
R20: 2R7; 0204/5
R24: 2R7; R1206
R25: 100; 0204/7
R45: 56R; R1206
R50: 6k8; 0204/7
R51: 3k3; 0204/7
S3: B3F-4150; TACTILE-PTH-12MM
U4: TLV70033; SOT23-5
U$1: BATTERY-CHARGER-LI-PROT
U$2: IRLML6244; MICRO3
U$3: HT7333; SOT89

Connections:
/RESET: C18.1, D6.A, R1.2; also elsewhere on the board
A9: C5.1, R3.2, R25.1, R26.2
AREF: C12.1, R50.1; also elsewhere on the board
B_MINUS: U$1.B-; also elsewhere on the board
CA_PWM1: D12.A, M2.3 (D)
CA_PWM2: D11.A, M12.3 (D)
D8_: JP6.4; also elsewhere on the board
D9_: JP6.5; also elsewhere on the board
D18_: R44.2; also elsewhere on the board
EN: C5.2, C10.1, R2.2, R3.1, R23.2, R26.1, R27.2, U4.3 (EN), U$2.1 (G)
EN_: D11.C, D12.C, R27.1
GND: C10.2, C11.2, C16.2, C20.C (-), C21.C (-), D1.A, D3.A, IC1.1 (GND), R2.1, R23.1, R51.1, S3.P$15 (5), U4.2 (GND), U$1.IN-, U$1.OUT-, U$3.GND
GND-ISO: C12.2, JP6.1, JP6.2, U$2.3 (D); also elsewhere on the board
unnamed: C11.1, U4.4 (BP)
unnamed: S3.P$3 (3), S3.P$4 (4), S3.P$13 (3), S3.P$14 (4), S3.P$23 (3), S3.P$24 (4)
unnamed: M2.1 (G), R28.2, R44.1
unnamed: M12.1 (G), R46.2, R47.1
unnamed: C18.2, D1.C, JP6.6, R51.2
unnamed: R45.2, U$1.IN+
VCC: C16.1, C20.A (+), D6.C, D7.A, D8.C, IC1.3 (VO), JP6.3, M2.2 (S), R1.1, R20.2, R24.2, R28.1, R50.2, U4.5 (OUT), U$3.VOUT; also elsewhere on the board
VIN_P: D9.A, D10.A, R45.1, R47.2
V_IN: C21.A (+), D3.C, D7.C, D9.C, IC1.2@1 (VI1), S3.P$1 (1), S3.P$2 (2), S3.P$11 (1), S3.P$12 (2), S3.P$21 (1), S3.P$22 (2), U4.1 (IN), U$1.B+, U$1.OUT+; also elsewhere on the board
XX_3: D8.A, D10.C, M12.2 (S), R20.1, R24.1, R46.1

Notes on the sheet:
Calculator 15-Digit with 1284P
by Jens Grabner
0.8
Calculator 15-Digit with ATmega1284P by Jens Grabner is licensed under
Copyright CERN 2013
the CERN OHL v.1.2 or later. (http://ohwr.org/cernohl)
Max Voltage Input: 10VDC
Max Current Output: 100mA
Board is marked with combination of
resonator frequency and regulator voltage.
VCC = 3.3V Output

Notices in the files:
parts and their libraries:
SparkFun-Connectors: Licensing: CC v3.0 Share-Alike You are welcome to use this library for commercial purposes.
SparkFun-Electromechanical: Licensing: Creative Commons ShareAlike 4.0 International - https://creativecommons.org/licenses/by-sa/4.0
